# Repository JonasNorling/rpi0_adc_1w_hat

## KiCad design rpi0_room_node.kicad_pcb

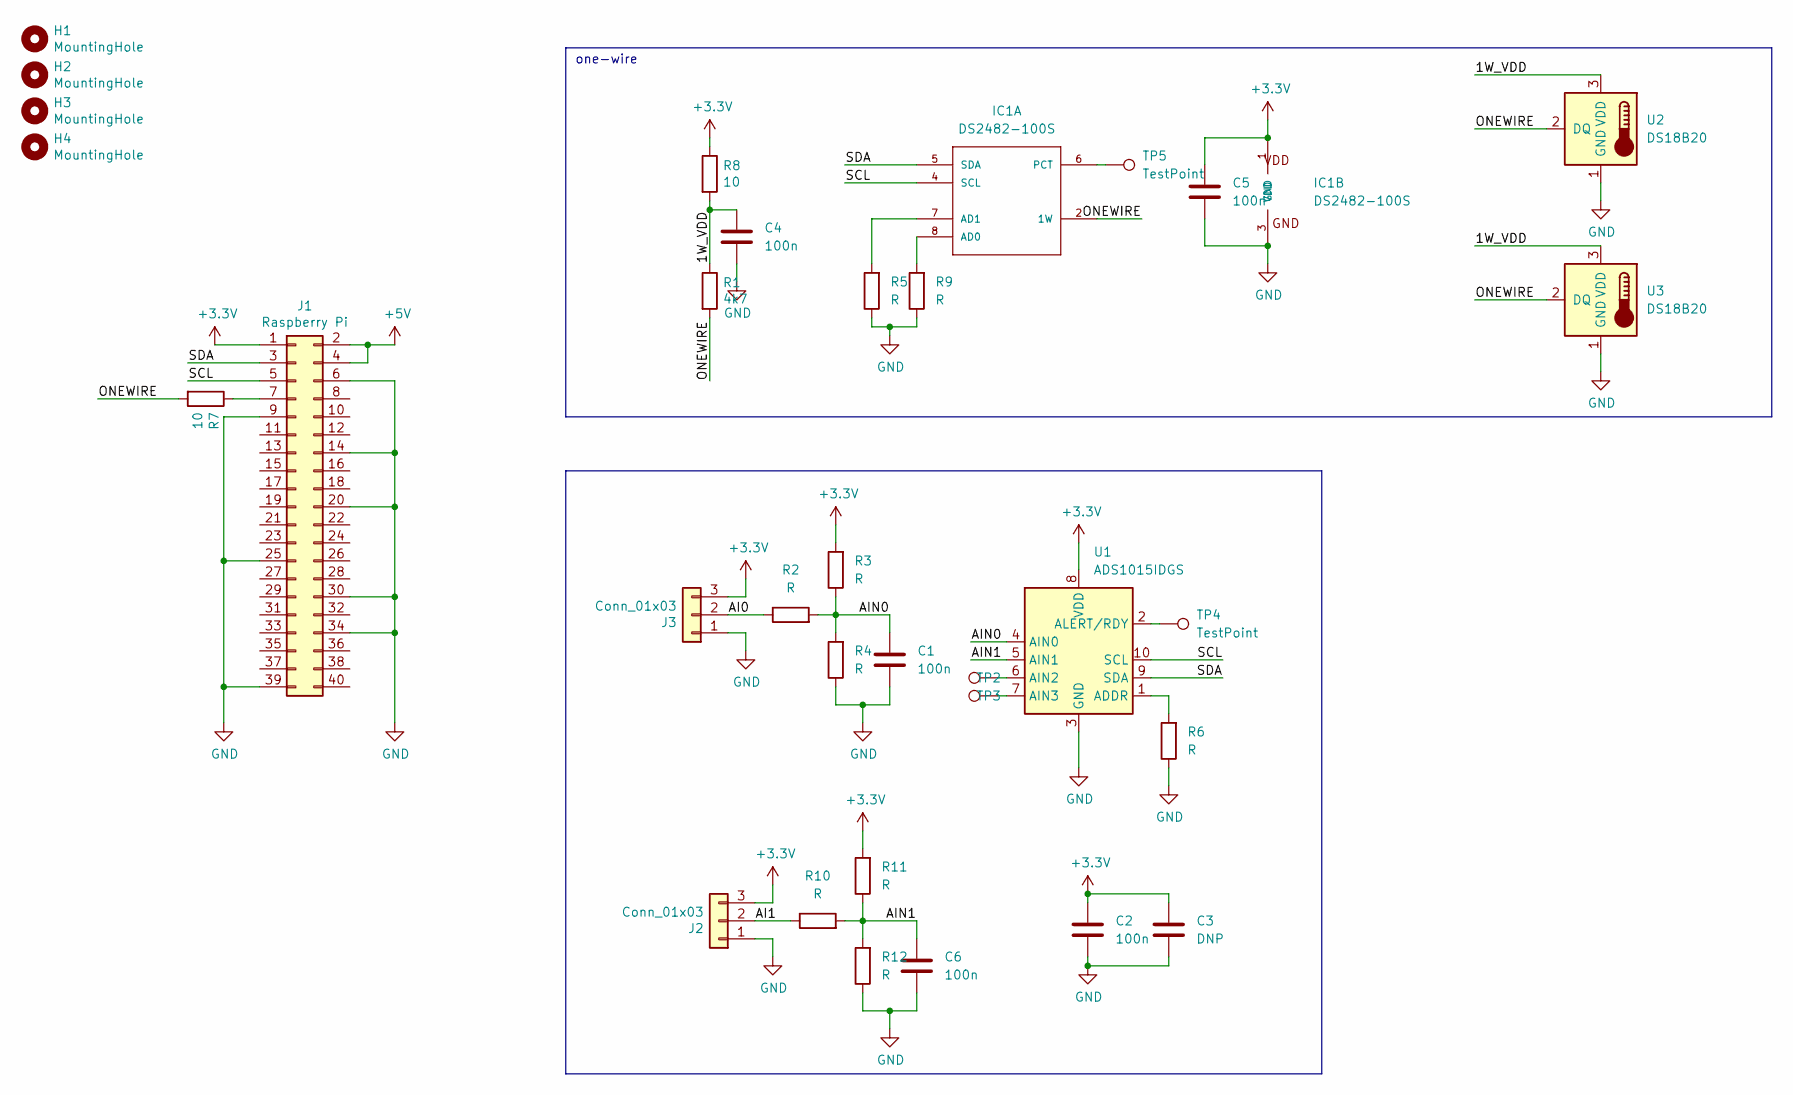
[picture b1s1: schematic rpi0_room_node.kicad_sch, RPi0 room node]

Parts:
C1, C6: 100n; C_0603_1608Metric_Pad1.08x0.95mm_HandSolder
C2, C4, C5: 100n; C_0402_1005Metric_Pad0.74x0.62mm_HandSolder
C3: DNP; C_0805_2012Metric_Pad1.18x1.45mm_HandSolder
H1, H2, H3, H4: MountingHole; hole_2.75
IC1: DS2482-100S; SO-8_3.9x4.9mm_P1.27mm
J1: Raspberry Pi; PinHeader_2x20_P2.54mm_Vertical
J2, J3: Conn_01x03; JST_PH_B3B-PH-SM4-TB_1x03-1MP_P2.00mm_Vertical + 2.54 mm he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
R1: 4k7; R_0402_1005Metric_Pad0.72x0.64mm_HandSolder
R2, R3, R4, R10, R11, R12: R; R_0603_1608Metric_Pad0.98x0.95mm_HandSolder
R5, R6, R9: R; NetTie-2_THT_Pad0.3mm
R7, R8: 10; R_0402_1005Metric_Pad0.72x0.64mm_HandSolder
TP2, TP3, TP4, TP5: TestPoint; PinHeader_1x01_P1.27mm_Vertical
U1: ADS1015IDGS; TSSOP-10_3x3mm_P0.5mm
U2, U3: DS18B20; JST_PH_B3B-PH-SM4-TB_1x03-1MP_P2.00mm_Vertical + 2.54 mm he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

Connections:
+3.3V: C2.1, C3.1, C5.2, IC1.1 (VDD), J1.1, J2.3, J3.3, R3.2, R8.1, R11.2, U1.8 (VDD)
+5V: J1.2, J1.4
/1W_VDD: C4.2, R1.1, R8.2, U2.3 (VDD), U3.3 (VDD)
/AI0: J3.2, R2.1
/AI1: J2.2, R10.1
/AIN0: C1.1, R2.2, R3.1, R4.2, U1.4 (AIN0)
/AIN1: C6.1, R10.2, R11.1, R12.2, U1.5 (AIN1)
/ONEWIRE: IC1.2 (1W), R1.2, R7.2, U2.2 (DQ), U3.2 (DQ)
/SCL: IC1.4 (SCL), J1.5, U1.10 (SCL)
/SDA: IC1.5 (SDA), J1.3, U1.9 (SDA)
GND: C1.2, C2.2, C3.2, C4.1, C5.1, C6.2, IC1.3 (GND), J1.6, J1.9, J1.14, J1.20, J1.25, J1.30, J1.34, J1.39, J2.1, J3.1, R4.1, R5.1, R6.1, R9.1, R12.1, U1.3 (GND), U2.1 (GND), U3.1 (GND)
unnamed: IC1.6 (PCT), TP5.1
unnamed: IC1.7 (AD1), R5.2
unnamed: IC1.8 (AD0), R9.2
unnamed: J1.7, R7.1
unnamed: R6.2, U1.1 (ADDR)
unnamed: TP2.1, U1.6 (AIN2)
unnamed: TP3.1, U1.7 (AIN3)
unnamed: TP4.1, U1.2 (ALERT/RDY)

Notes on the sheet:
one-wire

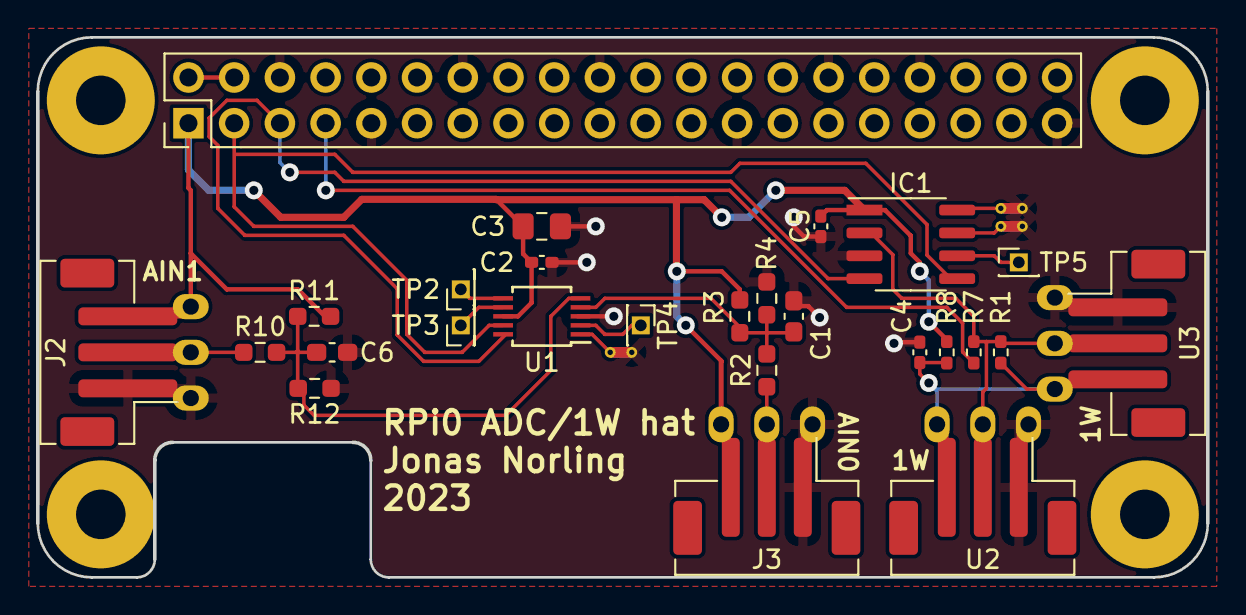
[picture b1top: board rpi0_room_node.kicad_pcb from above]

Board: 2 copper layers, 65.0 x 30.0 mm, 33 parts (0 on the bottom side), 19 nets.

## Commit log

2023-08-01 Convert to KiCad 6 format
2023-08-01 Add ADS1015 ADC
2023-08-01 Add one-wire chip
2023-08-02 Polishing
2023-08-03 Clean up, round corners
2023-08-04 Add 2.54 mm holes to JST connectors
2023-08-04 Move silkscreen texts
